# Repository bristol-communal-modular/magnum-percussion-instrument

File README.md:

# The Magnum Percussion Instrument

A drum synthesiser created by members of the Bristol Communal Modular group

## Description

Mostly combining bits from other open source schematics.

Specifically :-

* The Clacktronics Star Synare 3
* The Befaco Kickall

Many thanks to the people that designed those and made them open.

## Building

In the *build* folder there's an html BOM file, along with a CSV file that has part numbers for most components. Read the build.md file in there for more information. If you're reading this on GitHub and are unsure how to easily get these files, then [use this link](https://github.com/bristol-communal-modular/magnum-percussion-instrument/archive/refs/heads/main.zip)

## Spec

*Finish this*

### Power

30mA on +12v
30mA on -12v

Doesn't use 5v

## Contact

Come down the Bristol Hackspace on a Tuesday night to say hello.

## License

The Magnum Percussion Instrument is shared under an [Attribution-NonCommercial-ShareAlike 4.0 International License](https://creativecommons.org/licenses/by-nc-sa/4.0/)

This means that you can share the info here around, and transform or build upon the circuits and designs in here, as long as you share anything you do under the same license and give BCM a shout-out.

We don't license this for commercial purposes, but if you'd like to run a workshop with the Magnum or some variation of it, just get in contact and we can sort something out.
If you want to build a couple to sell to your mates then we're pretty fine with that as well.

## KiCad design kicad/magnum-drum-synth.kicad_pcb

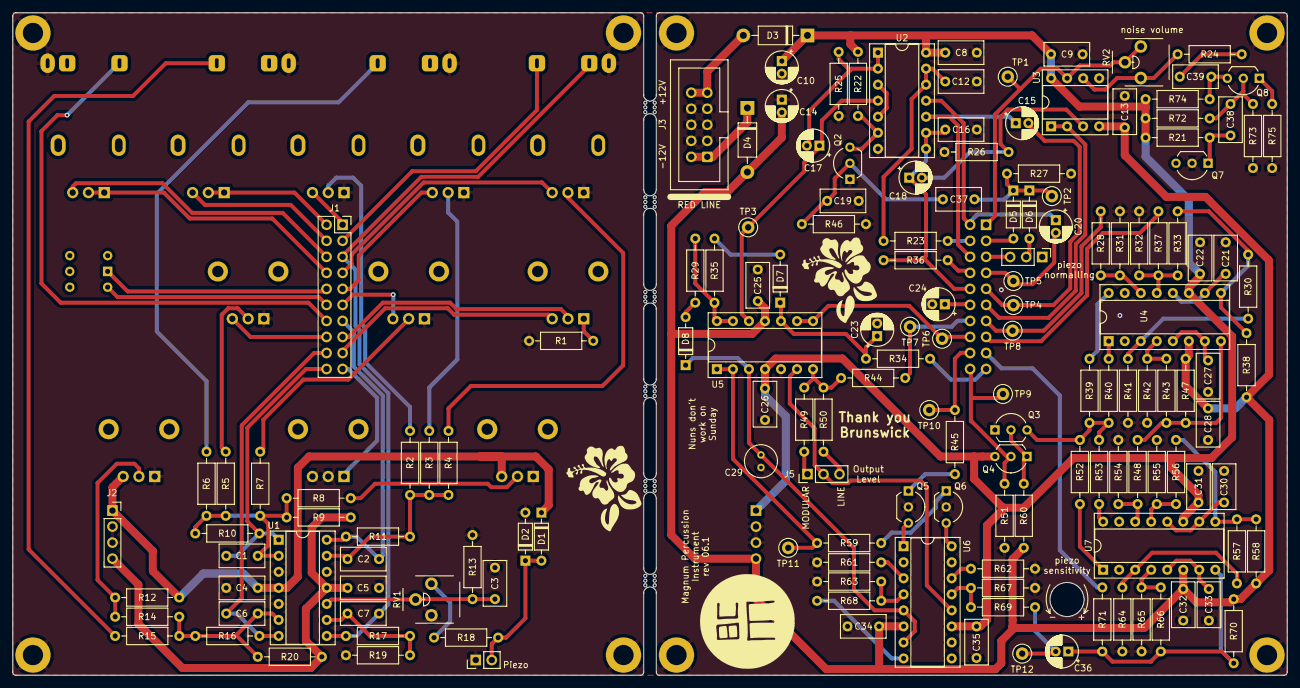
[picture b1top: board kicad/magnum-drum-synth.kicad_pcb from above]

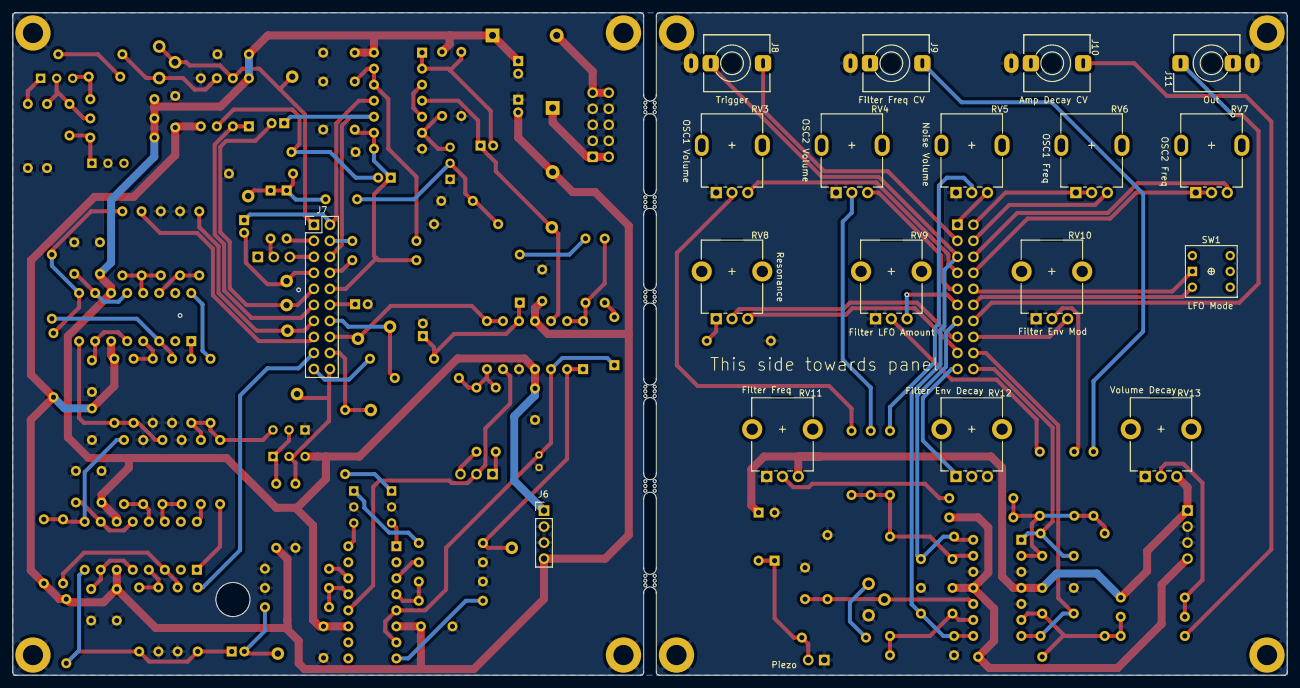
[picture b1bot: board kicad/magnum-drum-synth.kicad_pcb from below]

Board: 2 copper layers, 202.0 x 105.0 mm, 188 parts (18 on the bottom side), 119 nets.

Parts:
C1, C19: 10nF; C_Rect_L7.0mm_W3.5mm_P5.00mm
C2, C6, C7: 22pF; C_Rect_L7.0mm_W3.5mm_P5.00mm
C3: 220nF; C_Rect_L7.0mm_W3.5mm_P5.00mm
C4, C5, C8, C9, C13, C22, C25, C26, C28, C31, C32, C34, C35, C37, C38, C39: 100nF; C_Rect_L7.0mm_W3.5mm_P5.00mm
C10, C14, C23, C36: 10uF; CP_Radial_D5.0mm_P2.00mm
C12, C16: 47nF; C_Rect_L7.0mm_W3.5mm_P5.00mm
C15, C17, C18, C20, C24: 1uF; CP_Radial_D5.0mm_P2.00mm
C21, C27, C30, C33: 100pF; C_Rect_L7.0mm_W3.5mm_P5.00mm
C29: 1uF; C_Radial_D5.0mm_H5.0mm_P2.00mm
D1, D2, D5, D6, D7, D8: 1N4148; D_DO-35_SOD27_P7.62mm_Horizontal
D3, D4: 1N5818; D_DO-41_SOD81_P10.16mm_Horizontal
H1, H2, H9, H10, H13, H14, H15, H16: MountingHole_Pad; MountingHole_3.2mm_M3_DIN965_Pad
H3, H4, H5, H6, H7, H8: MouseBite; mouse-bite-2mm-slot
J1: Conn_02x10_Odd_Even; PinSocket_2x10_P2.54mm_Vertical
J2: Conn_01x04_Socket; PinSocket_1x04_P2.54mm_Vertical
J3: locked; Eurorack_PowerHeader_2x05_P2.54mm_Shrouded
J4, J5: Conn_01x03_Header; PinHeader_1x03_P2.54mm_Vertical
J6: Conn_01x04_Header; PinHeader_1x04_P2.54mm_Vertical
J7: Conn_02x10_Odd_Even; PinHeader_2x10_P2.54mm_Vertical
J8, J9, J10, J11: Eurorack Mono Jack; Jack_3.5mm_QingPu_WQP-PJ398SM_Vertical
MK1: Piezo; PinHeader_1x02_P2.54mm_Vertical
Q2, Q4, Q7, Q8: 2N3904; TO-92_Inline_Wide
Q3, Q5, Q6: 2N3906; TO-92_Inline_Wide
R1, R5: 47k; R_Axial_DIN0207_L6.3mm_D2.5mm_P10.16mm_Horizontal
R2, R3, R4, R6, R7, R8, R11, R15, R20, R21, R27, R28, R30, R33, R43, R48, R56, R57, R60, R66, R69, R73: 100k; R_Axial_DIN0207_L6.3mm_D2.5mm_P10.16mm_Horizontal
R9, R26: 220k; R_Axial_DIN0207_L6.3mm_D2.5mm_P10.16mm_Horizontal
R10: 2k; R_Axial_DIN0207_L6.3mm_D2.5mm_P10.16mm_Horizontal
R12, R23, R36, R39, R40, R52, R53: 22k; R_Axial_DIN0207_L6.3mm_D2.5mm_P10.16mm_Horizontal
R13: 1m; R_Axial_DIN0207_L6.3mm_D2.5mm_P10.16mm_Horizontal
R14: 120k; R_Axial_DIN0207_L6.3mm_D2.5mm_P10.16mm_Horizontal
R16: 27k; R_Axial_DIN0207_L6.3mm_D2.5mm_P10.16mm_Horizontal
R17, R68: 33k; R_Axial_DIN0207_L6.3mm_D2.5mm_P10.16mm_Horizontal
R18, R34, R51: 1k; R_Axial_DIN0207_L6.3mm_D2.5mm_P10.16mm_Horizontal
R19, R22, R24, R25, R38, R46, R47, R58, R70, R71, R74: 10k; R_Axial_DIN0207_L6.3mm_D2.5mm_P10.16mm_Horizontal
R29: 100r; R_Axial_DIN0207_L6.3mm_D2.5mm_P10.16mm_Horizontal
R31, R32, R41, R42, R54, R55, R62, R64, R65, R67: 220r; R_Axial_DIN0207_L6.3mm_D2.5mm_P10.16mm_Horizontal
R35: 47r; R_Axial_DIN0207_L6.3mm_D2.5mm_P10.16mm_Horizontal
R37: 6k8; R_Axial_DIN0207_L6.3mm_D2.5mm_P10.16mm_Horizontal
R44, R61, R63: 470r; R_Axial_DIN0207_L6.3mm_D2.5mm_P10.16mm_Horizontal
R45: 4k7; R_Axial_DIN0207_L6.3mm_D2.5mm_P10.16mm_Horizontal
R49: 56k; R_Axial_DIN0207_L6.3mm_D2.5mm_P10.16mm_Horizontal
R50: 12k; R_Axial_DIN0207_L6.3mm_D2.5mm_P10.16mm_Horizontal
R59: 18k; R_Axial_DIN0207_L6.3mm_D2.5mm_P10.16mm_Horizontal
R72: 560k; R_Axial_DIN0207_L6.3mm_D2.5mm_P10.16mm_Horizontal
R75: 22r; R_Axial_DIN0207_L6.3mm_D2.5mm_P10.16mm_Horizontal
RV1: 100k; Potentiometer_THT_Bourns_3306P_Vertical
RV2: 1m; Potentiometer_THT_Bourns_3306P_Vertical
RV3, RV4, RV5: 100kA; Potentiometer_Song_Huei_R0904N_Single_Vertical
RV6, RV7: 1mA; Potentiometer_Song_Huei_R0904N_Single_Vertical
RV8: 50kB; Potentiometer_Alpha_RD901F-40-00D_Single_Vertical_CircularH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
RV9, RV10, RV11, RV12, RV13: 100kB; Potentiometer_Alpha_RD901F-40-00D_Single_Vertical_CircularH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
Ref**1: Val**; BCM_Logo_small_15mmx15mm
SW1: DPDT; SW_PUSH_2P2T_8mm_Apem_MHPS2285
TP1: Noise TestPoint; TestPoint_Loop_D2.50mm_Drill1.0mm_LowProfile
TP2: Trigger TestPoint; TestPoint_Loop_D2.50mm_Drill1.0mm_LowProfile
TP3, TP10: Schmitt Trigger TestPoint; TestPoint_Loop_D2.50mm_Drill1.0mm_LowProfile
TP4: OSC2 TestPoint; TestPoint_Loop_D2.50mm_Drill1.0mm_LowProfile
TP5: OSC1 TestPoint; TestPoint_Loop_D2.50mm_Drill1.0mm_LowProfile
TP6: Filter Envelope TestPoint; TestPoint_Loop_D2.50mm_Drill1.0mm_LowProfile
TP7: Final Output TestPoint; TestPoint_Loop_D2.50mm_Drill1.0mm_LowProfile
TP8: Mixer TestPoint; TestPoint_Loop_D2.50mm_Drill1.0mm_LowProfile
TP9: Filter CV Mixer TestPoint; TestPoint_Loop_D2.50mm_Drill1.0mm_LowProfile
TP11: VCA Envelope TestPoint; TestPoint_Loop_D2.50mm_Drill1.0mm_LowProfile
TP12: Filter Output TestPoint; TestPoint_Loop_D2.50mm_Drill1.0mm_LowProfile
U1, U5: TL074; DIP-14_W7.62mm_Socket
U2: CD4093; DIP-14_W7.62mm_Socket
U3: TL072; DIP-8_W7.62mm_Socket
U4, U6, U7: LM13700; DIP-16_W7.62mm_Socket

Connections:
+12V: C4.1, C8.1, C9.1, C10.1, C22.1, C26.1, C31.1, C35.1, D1.1 (K), D3.1 (K), J2.1, J6.1, Q4.3 (C), R12.2, R21.1, R22.1, R72.2, R74.2, RV11.3, RV13.3, U1.4 (V+), U2.14 (VCC), U3.8 (V+), U4.11 (V+), U5.4 (V+), U6.11 (V+), U7.11 (V+)
-12V: C5.2, C13.2, C14.2, C25.2, C28.2, C32.2, C34.2, D4.2 (A), J2.4, J6.4, R9.1, R20.1, R38.2, R47.2, R58.2, R60.1, R70.2, U1.11 (V-), U3.4 (V-), U4.6 (V-), U5.11 (V-), U6.6 (V-), U7.6 (V-)
/AMP_DECAY_CV_MIX_CTRL: C6.2, J1.18, R16.2, U1.7
/AMP_DECAY_CV_MIX_MAIN: J7.18, R45.1, TP10.1
/FILTER_ENV_DECAY_CTRL: J1.19, RV12.1
/FILTER_ENV_DECAY_MAIN: J7.19, R34.2
/FILTER_ENV_MOD_CTRL: J1.16, RV10.3
/FILTER_ENV_MOD_MAIN: J7.16, TP6.1, U5.8, U5.9 (-)
/FILTER_FREQ_CV_CTRL: C1.2, J1.20, R10.2, U1.1
/FILTER_FREQ_CV_MAIN: J7.20, Q4.2 (B), R51.1, TP9.1
/FINAL_OUTPUT_CTRL: J1.14, J11.2 (Tip)
/FINAL_OUTPUT_MAIN: J7.14, R44.2, TP7.1
/Filter/I_Freq: Q3.3 (C), R39.2, R40.2, R52.2, R53.2
/Filter/Output: C36.1, R66.2, R70.1, R71.1, U7.8
/MIX_RETURN_CTRL: C2.2, J1.13, R11.2, U1.14
/MIX_RETURN_MAIN: J7.13, R28.1, TP8.1
/NOISE_SIGNAL_CTRL: J1.1, RV5.3
/NOISE_SIGNAL_MAIN: J7.1, RV2.2, RV2.3, TP1.1, U3.7
/OSC1_FREQ_L_CTRL: J1.4, RV6.3
/OSC1_FREQ_L_MAIN: J7.4, R23.2
/OSC1_FREQ_R_CTRL: J1.2, RV6.1, RV6.2
/OSC1_FREQ_R_MAIN: C20.1, J7.2, U2.11
/OSC1_SIGNAL_CTRL: J1.7, RV3.3
/OSC1_SIGNAL_MAIN: C20.2, J7.7, TP5.1
/OSC2_FILTER_MOD_CTRL: J1.11, RV9.3
/OSC2_FILTER_MOD_MAIN: J7.11, U3.1, U3.2 (-)
/OSC2_FREQ_L_CTRL: J1.8, RV7.1, RV7.2
/OSC2_FREQ_L_MAIN: J7.8, R36.2
/OSC2_FREQ_R_CTRL: J1.6, RV7.3
/OSC2_FREQ_R_MAIN: C15.1, J7.6, U2.10
/OSC2_LFO_CAP_CTRL: J1.12, SW1.2 (B)
/OSC2_LFO_CAP_MAIN: C24.1, J7.12
/OSC2_LFO_CTRL: J1.10, SW1.1 (A)
/OSC2_LFO_MAIN: C16.1, C18.1, J7.10, R36.1, U2.8, U2.9
/OSC2_SIGNAL_CTRL: J1.9, RV4.3
/OSC2_SIGNAL_MAIN: C15.2, J7.9, TP4.1
/OutputVCA/I_Gain: Q6.3 (C), U6.16
/OutputVCA/Input: C36.2, R69.1, TP12.1
/OutputVCA/Output: R44.1, R49.2, R50.2, U5.7
/PIEZO_CTRL: C7.2, J1.5, J8.3 (Tip_normalize), R17.1, U1.8
/PIEZO_MAIN: J4.3, J7.5
/RES_AMOUNT_CTRL: J1.15, RV8.2
/RES_AMOUNT_MAIN: J7.15, R37.1
/RES_TOP_CTRL: J1.17, RV8.3
/RES_TOP_MAIN: J7.17, R71.2
/TRIG_IN_CTRL: J1.3, J8.2 (Tip)
/TRIG_IN_MAIN: D5.2 (A), J7.3
/Trigger: R29.1, R35.1, U5.13 (-), U5.14
GND: C3.1, C4.2, C5.1, C8.2, C9.2, C10.2, C12.1, C13.1, C14.1, C16.2, C19.1, C21.1, C22.2, C23.2, C24.2, C25.1, C26.2, C27.1, C28.1, C29.2, C30.1, C31.2, C32.1, C33.1, C34.1, C35.2, D2.2 (A), H1.1, H2.1, H9.1, H10.1, H13.1, H14.1, H15.1, H16.1, J2.2, J2.3, J3.3 (GND), J3.4 (GND), J3.5 (GND), J3.6 (GND), J3.7 (GND), J3.8 (GND), J6.2, J6.3, J8.1 (Sleeve), J9.1 (Sleeve), J10.1 (Sleeve), J11.1 (Sleeve), MK1.1 (-), Q2.1 (E), Q3.1 (E), Q5.2 (B), Q6.2 (B), Q7.2 (B), R1.2, R13.2, R19.1, R25.2, R26.1, R27.1, R31.2, R32.2, R41.2, R42.2, R46.2, R51.2, R54.2, R55.2, R61.1, R62.2, R63.1, R64.2, R65.2, R67.2, R73.1, R75.1, RV1.1, RV3.1, RV4.1, RV5.1, RV9.1, RV10.1, RV11.1, RV12.2, RV12.3, RV13.1, U1.3 (+), U1.5 (+), U1.12 (+), U2.7 (GND), U3.5 (+), U5.5 (+)
unnamed: C12.2, R23.1, U2.12, U2.13
unnamed: C17.2, R25.1, U2.1, U2.2
unnamed: C21.2, U4.10, U4.12
unnamed: C27.2, U4.5, U4.7
unnamed: C30.2, U7.10, U7.12
unnamed: C33.2, U7.5, U7.7
unnamed: C39.2, R24.1
unnamed: D1.2 (A), D2.1 (K), MK1.2 (+), R18.1
unnamed: D3.2 (A), J3.9 (+12V), J3.10 (+12V)
unnamed: D4.1 (K), J3.1 (-12V), J3.2 (-12V)
unnamed: C37.2, D5.1 (K), D6.1 (K), R27.2, TP2.1
unnamed: D6.2 (A), J4.2
unnamed: D7.2 (A), R35.2
unnamed: C23.1, D7.1 (K), R34.1, U5.10 (+)
unnamed: D8.2 (A), R29.2
unnamed: C29.1, D8.1 (K), U5.3 (+), U6.5, U6.7
unnamed: J5.1, R49.1
unnamed: J5.2, U5.6 (-), U6.12
unnamed: J5.3, R50.1
unnamed: J9.2 (Tip), R6.1
unnamed: J10.2 (Tip), R15.1
unnamed: C19.2, C37.1, Q2.2 (B), R46.1
unnamed: Q2.3 (C), R22.2, U2.6
unnamed: Q3.2 (B), Q4.1 (E), R60.2
unnamed: Q5.3 (C), U6.1
unnamed: Q5.1 (E), R45.2
unnamed: Q6.1 (E), R59.2
unnamed: C38.1, Q7.1 (E), R21.2
unnamed: C38.2, Q8.2 (B), R72.1, R73.2
unnamed: C39.1, Q8.3 (C), R74.1
unnamed: Q8.1 (E), R75.2
unnamed: R1.1, RV8.1
unnamed: R2.1, RV5.2
unnamed: R3.1, RV4.2
unnamed: R4.1, RV3.2
unnamed: R5.1, RV10.2
unnamed: R7.1, RV9.2
unnamed: R8.1, RV11.2
unnamed: R12.1, R14.2, RV13.2
unnamed: R18.2, RV1.3
unnamed: R30.1, R33.2, R38.1, U4.9
unnamed: R39.1, U4.16
unnamed: R40.1, U4.1
unnamed: R43.2, R47.1, R48.1, U4.8
unnamed: R52.1, U7.1
unnamed: R53.1, U7.16
unnamed: R56.2, R57.1, R58.1, U7.9
unnamed: R68.2, U6.8
unnamed: C1.1, R5.2, R6.2, R7.2, R8.2, R9.2, R10.1, U1.2 (-)
unnamed: C6.1, R14.1, R15.2, R16.1, R20.2, U1.6 (-)
unnamed: C3.2, R13.1, RV1.2, U1.10 (+)
unnamed: C7.1, R17.2, R19.2, U1.9 (-)
unnamed: C2.1, R2.2, R3.2, R4.2, R11.1, U1.13 (-)
unnamed: U2.3, U2.5
unnamed: C18.2, R26.2, U3.3 (+)
unnamed: R24.2, RV2.1, U3.6 (-)
unnamed: R28.2, R31.1, U4.14 (+)
unnamed: R32.1, R33.1, R37.2, U4.13 (-)
unnamed: R30.2, R41.1, U4.3 (+)
unnamed: R42.1, R43.1, U4.4 (-)
unnamed: R59.1, TP11.1, U5.1, U5.2 (-)
unnamed: C17.1, TP3.1, U2.4, U5.12 (+)
unnamed: R62.1, U6.14 (+)
unnamed: R67.1, R69.2, U6.13 (-)
unnamed: R61.2, U6.3 (+)
unnamed: R63.2, R68.1, U6.4 (-)
unnamed: R48.2, R54.1, U7.14 (+)
unnamed: R55.1, R56.1, U7.13 (-)
unnamed: R57.2, R64.1, U7.3 (+)
unnamed: R65.1, R66.1, U7.4 (-)

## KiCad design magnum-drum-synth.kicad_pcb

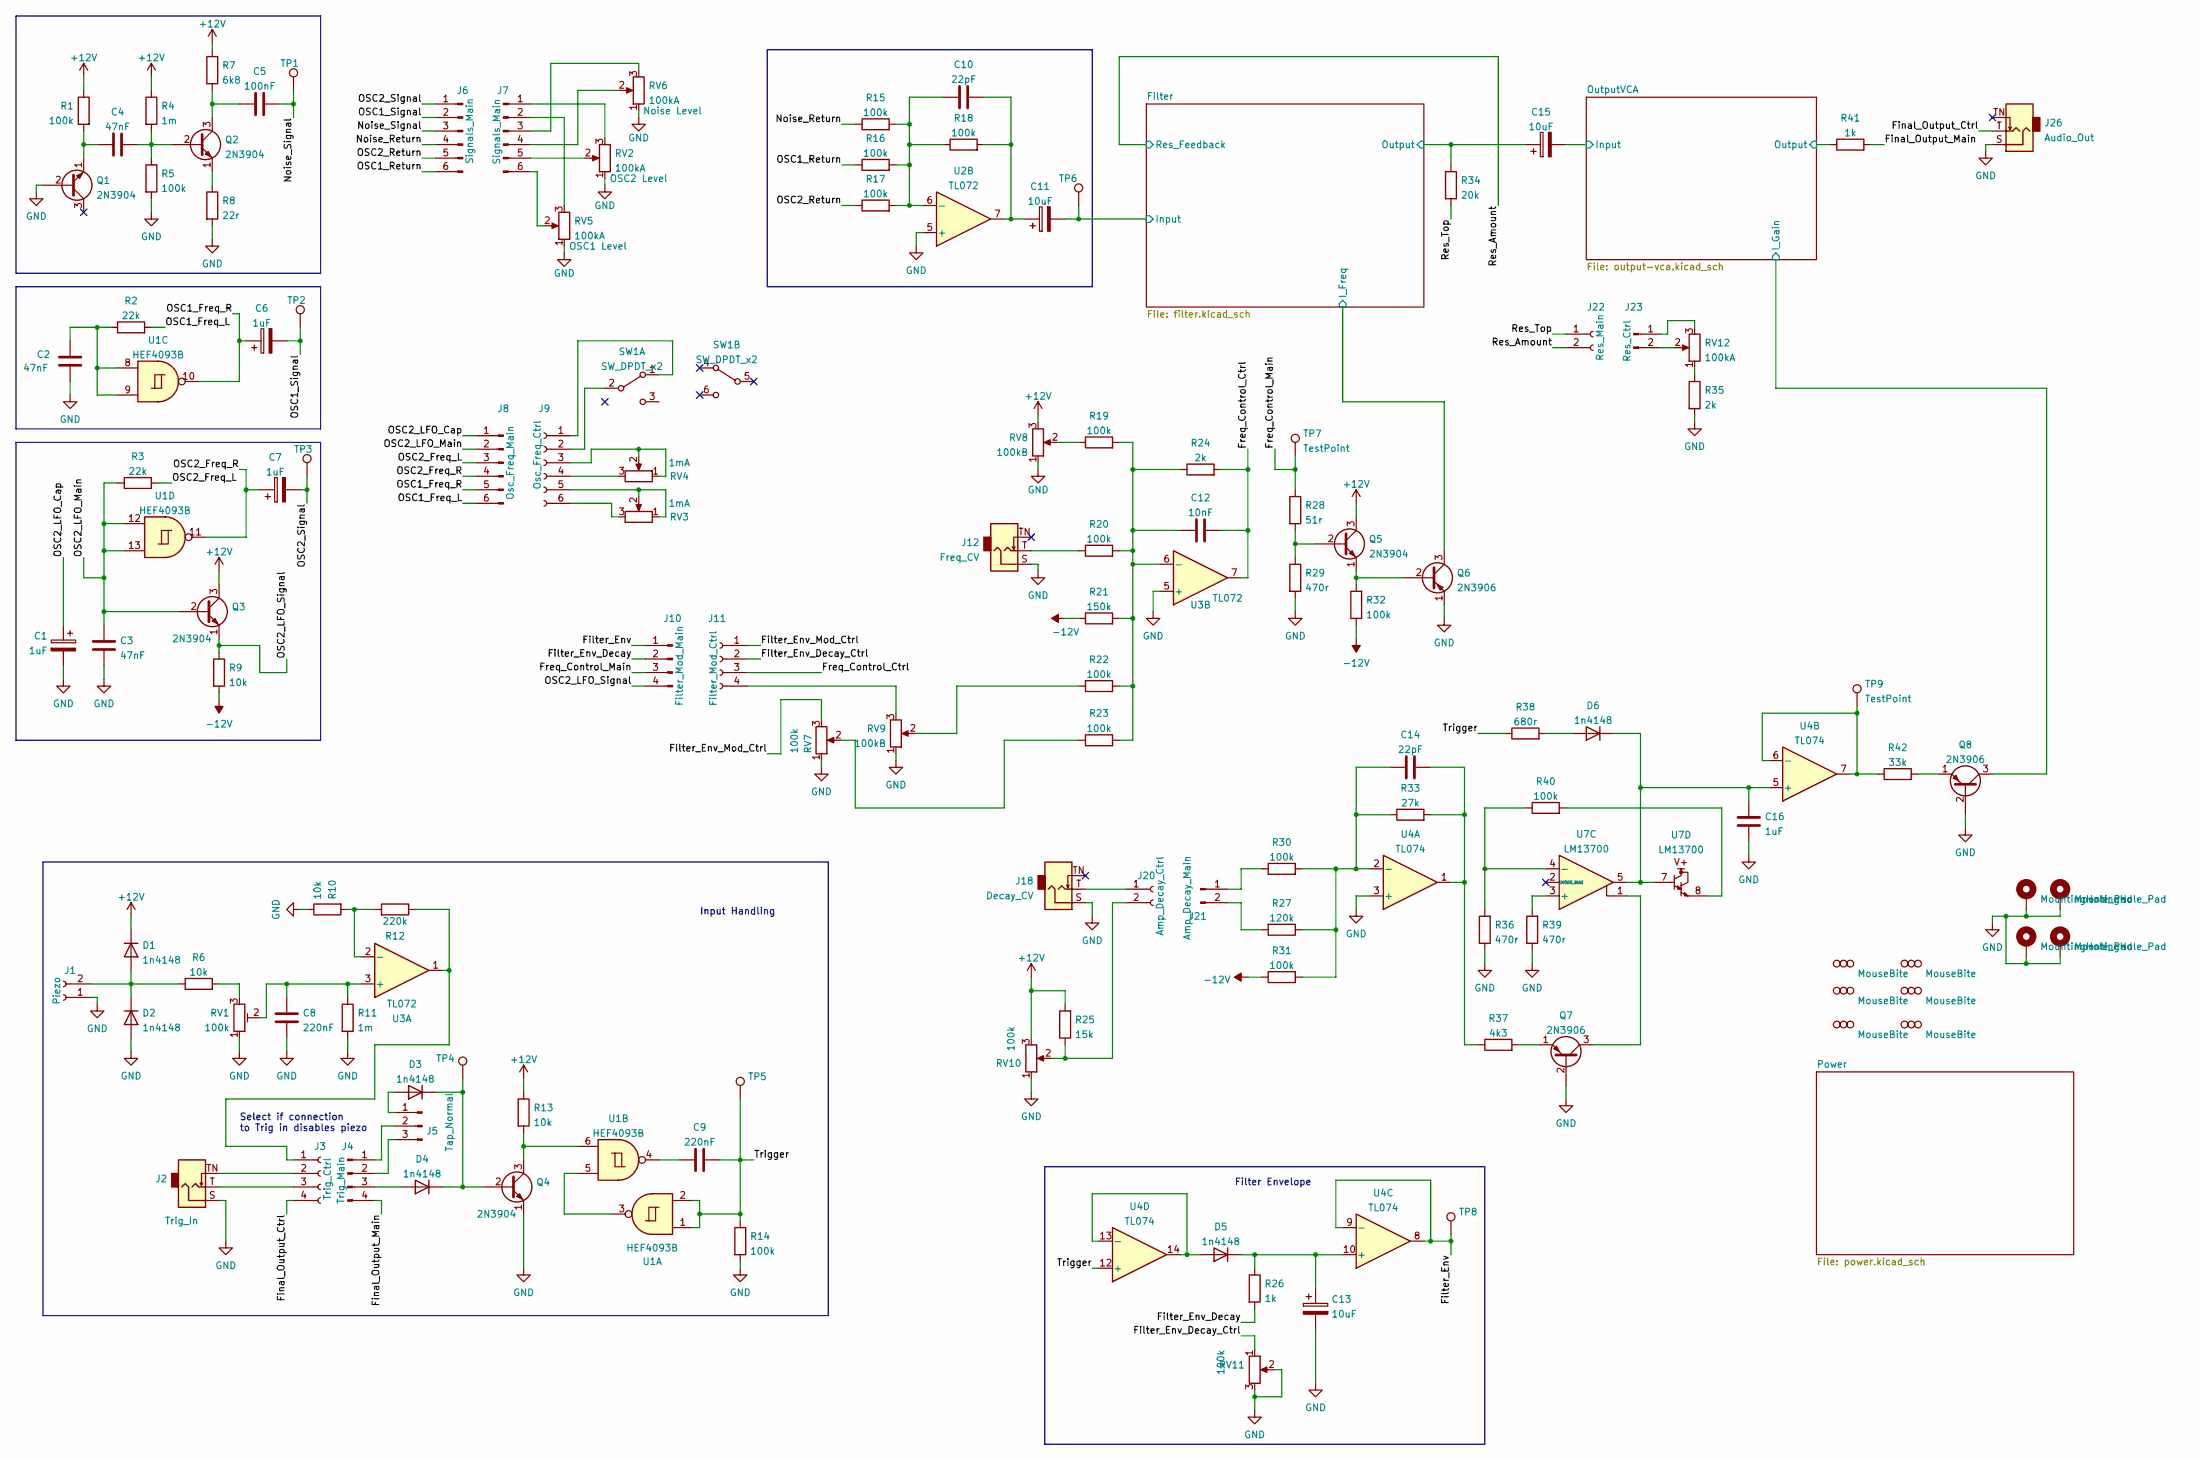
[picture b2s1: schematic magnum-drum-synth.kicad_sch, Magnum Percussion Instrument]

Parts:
C1, C6, C7: 1uF; CP_Radial_D5.0mm_P2.50mm
C2, C3, C4: 47nF; C_Rect_L7.0mm_W3.5mm_P5.00mm
C5: 100nF; C_Rect_L7.0mm_W3.5mm_P5.00mm
C8, C9: 220nF; C_Rect_L7.0mm_W3.5mm_P5.00mm
C10, C14: 22pF; C_Rect_L7.0mm_W3.5mm_P5.00mm
C11, C13, C15: 10uF; CP_Radial_D5.0mm_P2.50mm
C12: 10nF; C_Rect_L7.0mm_W3.5mm_P5.00mm
C16: 1uF; C_Radial_D6.3mm_H7.0mm_P2.50mm
D1, D2, D3, D4, D5, D6: 1n4148; Diode_THT_P7.62mm_Horizontal
H1, H2, H3, H4, H5, H6: MouseBite; mouse-bite-2mm-slot
H7, H8, H9, H10: MountingHole_Pad; MountingHole_3.2mm_M3_ISO7380_Pad
J1: Piezo; PinHeader_1x02_P2.54mm_Vertical
J2: Trig_In; Jack_3.5mm_QingPu_WQP-PJ398SM_Vertical
J3: Trig_Ctrl; PinSocket_1x04_P2.54mm_Vertical
J4: Trig_Main; PinHeader_1x04_P2.54mm_Vertical
J5: Tap_Normal; PinHeader_1x03_P2.54mm_Vertical
J6, J7: Signals_Main; PinSocket_1x06_P2.54mm_Vertical
J8: Osc_Freq_Main; PinHeader_1x06_P2.54mm_Vertical
J9: Osc_Freq_Ctrl; PinSocket_1x06_P2.54mm_Vertical
J10: Filter_Mod_Main; PinSocket_1x04_P2.54mm_Vertical
J11: Filter_Mod_Ctrl; PinSocket_1x04_P2.54mm_Vertical
J12: Freq_CV; Jack_3.5mm_QingPu_WQP-PJ398SM_Vertical
J18: Decay_CV; Jack_3.5mm_QingPu_WQP-PJ398SM_Vertical
J20: Amp_Decay_Ctrl; PinSocket_1x02_P2.54mm_Vertical
J21: Amp_Decay_Main; PinHeader_1x02_P2.54mm_Vertical
J22: Res_Main; PinHeader_1x02_P2.54mm_Vertical
J23: Res_Ctrl; PinSocket_1x02_P2.54mm_Vertical
J26: Audio_Out; Jack_3.5mm_QingPu_WQP-PJ398SM_Vertical
Q1, Q2, Q3, Q4, Q5: 2N3904; TO-92_Inline_Wide
Q6, Q7, Q8: 2N3906; TO-92_Inline_Wide
R1, R5, R14, R15, R16, R17, R18, R19, R20, R22, R23, R30, R31, R32, R40: 100k; Resistor_THT_L6.3mm_D2.5mm_P10.16mm_Horizontal
R2, R3: 22k; Resistor_THT_L6.3mm_D2.5mm_P10.16mm_Horizontal
R4, R11: 1m; Resistor_THT_L6.3mm_D2.5mm_P10.16mm_Horizontal
R6, R9, R10, R13: 10k; Resistor_THT_L6.3mm_D2.5mm_P10.16mm_Horizontal
R7: 6k8; Resistor_THT_L6.3mm_D2.5mm_P10.16mm_Horizontal
R8: 22r; Resistor_THT_L6.3mm_D2.5mm_P10.16mm_Horizontal
R12: 220k; Resistor_THT_L6.3mm_D2.5mm_P10.16mm_Horizontal
R21: 150k; Resistor_THT_L6.3mm_D2.5mm_P10.16mm_Horizontal
R24, R35: 2k; Resistor_THT_L6.3mm_D2.5mm_P10.16mm_Horizontal
R25: 15k; Resistor_THT_L6.3mm_D2.5mm_P10.16mm_Horizontal
R26, R41: 1k; Resistor_THT_L6.3mm_D2.5mm_P10.16mm_Horizontal
R27: 120k; Resistor_THT_L6.3mm_D2.5mm_P10.16mm_Horizontal
R28: 51r; Resistor_THT_L6.3mm_D2.5mm_P10.16mm_Horizontal
R29, R36, R39: 470r; Resistor_THT_L6.3mm_D2.5mm_P10.16mm_Horizontal
R33: 27k; Resistor_THT_L6.3mm_D2.5mm_P10.16mm_Horizontal
R34: 20k; Resistor_THT_L6.3mm_D2.5mm_P10.16mm_Horizontal
R37: 4k3; Resistor_THT_L6.3mm_D2.5mm_P10.16mm_Horizontal
R38: 680r; Resistor_THT_L6.3mm_D2.5mm_P10.16mm_Horizontal
R42: 33k; Resistor_THT_L6.3mm_D2.5mm_P10.16mm_Horizontal
RV1: 100k; Potentiometer_THT_Bourns_3306P_Vertical
RV2, RV5, RV6: 100kA; Potentiometer_Alpha_RD901F-40-00D_Single_Vertical
RV3, RV4: 1mA; Potentiometer_Alpha_RD901F-40-00D_Single_Vertical
RV7, RV10, RV11: 100k; Potentiometer_Alpha_RD901F-40-00D_Single_Vertical_CircularH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
RV8, RV9: 100kB; Potentiometer_Alpha_RD901F-40-00D_Single_Vertical_CircularH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
RV12: 100kA; Potentiometer_Alpha_RD901F-40-00D_Single_Vertical_CircularH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
SW1: SW_DPDT_x2; SW_PUSH_2P2T_8mm_Apem_MHPS2285
TP1: Noise TestPoint; TestPoint_Loop_D2.50mm_Drill1.0mm_LowProfile
TP2: OSC1 TestPoint; TestPoint_Loop_D2.50mm_Drill1.0mm_LowProfile
TP3: OSC2 TestPoint; TestPoint_Loop_D2.50mm_Drill1.0mm_LowProfile
TP4: Trigger TestPoint; TestPoint_Loop_D2.50mm_Drill1.0mm_LowProfile
TP5: Schmitt Trigger TestPoint; TestPoint_Loop_D2.50mm_Drill1.0mm_LowProfile
TP6: Mixer TestPoint; TestPoint_Loop_D2.50mm_Drill1.0mm_LowProfile
TP7, TP9: TestPoint; TestPoint_Loop_D2.50mm_Drill1.0mm_LowProfile
TP8: Filter Env TestPoint; TestPoint_Loop_D2.50mm_Drill1.0mm_LowProfile
U1: HEF4093B; DIP-14_W7.62mm_LongPads
U2, U3: TL072; DIP-8_W7.62mm_LongPads
U4: TL074; DIP-14_W7.62mm_LongPads
U7: LM13700; DIP-16_W7.62mm_LongPads

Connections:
+12V: D1.1 (K), Q3.3 (C), Q5.3 (C), R1.1, R4.1, R7.1, R13.1, R25.2, RV8.3, RV10.3; also elsewhere on the board
-12V: R9.2, R21.1, R31.1, R32.1; also elsewhere on the board
/Filter/I_Freq: Q6.3 (C); also elsewhere on the board
/Filter/Input: C11.2, TP6.1; also elsewhere on the board
/Filter/Output: C15.1, R34.1; also elsewhere on the board
/Filter_Env: J10.1, TP8.1, U4.8, U4.9 (-)
/Filter_Env_Decay: J10.2, R26.2
/Filter_Env_Decay_Ctrl: J11.2, RV11.1
/Filter_Env_Mod_Ctrl: J11.1, RV7.3
/Final_Output_Ctrl: J3.4, J26.T
/Final_Output_Main: J4.4, R41.2
/Freq_Control_Ctrl: C12.2, J11.3, R24.2, U3.7
/Freq_Control_Main: J10.3, R28.1, TP7.1
/Noise_Return: J6.4, R15.1
/Noise_Signal: C5.2, J6.3, TP1.1
/OSC1_Freq_L: J8.6, R2.2
/OSC1_Freq_R: C6.1, J8.5, U1.10
/OSC1_Return: J6.6, R16.1
/OSC1_Signal: C6.2, J6.2, TP2.1
/OSC2_Freq_L: J8.3, R3.2
/OSC2_Freq_R: C7.1, J8.4, U1.11
/OSC2_LFO_Cap: C1.1, J8.1
/OSC2_LFO_Main: C3.1, J8.2, Q3.2 (B), R3.1, U1.12, U1.13
/OSC2_LFO_Signal: J10.4, Q3.1 (E), R9.1
/OSC2_Return: J6.5, R17.1
/OSC2_Signal: C7.2, J6.1, TP3.1
/OutputVCA/I_Gain: Q8.3 (C); also elsewhere on the board
/OutputVCA/Input: C15.2; also elsewhere on the board
/OutputVCA/Output: R41.1; also elsewhere on the board
/Res_Amount: J22.2; also elsewhere on the board
/Res_Top: J22.1, R34.2
/Trigger: C9.2, R14.1, R38.1, TP5.1, U1.1, U1.2, U4.12 (+)
GND: C1.2, C2.1, C3.2, C8.1, C13.2, C16.2, D2.2 (A), H7.1, H8.1, H9.1, H10.1, J1.1, J2.S, J12.S, J18.S, J26.S, Q1.2 (B), Q4.1 (E), Q6.1 (E), Q7.2 (B), Q8.2 (B), R5.2, R8.2, R10.1, R11.2, R14.2, R29.2, R35.2, R36.1, R39.1, RV1.1, RV2.1, RV5.1, RV6.1, RV7.1, RV8.1, RV9.1, RV10.1, RV11.2, RV11.3, U2.5 (+), U3.5 (+), U4.3 (+); also elsewhere on the board
unnamed: C2.2, R2.1, U1.8, U1.9
unnamed: C4.1, Q1.1 (E), R1.2
unnamed: C4.2, Q2.2 (B), R4.2, R5.1
unnamed: C5.1, Q2.3 (C), R7.2
unnamed: C8.2, R11.1, RV1.2, U3.3 (+)
unnamed: C9.1, U1.4
unnamed: C10.1, R15.2, R16.2, R17.2, R18.1, U2.6 (-)
unnamed: C10.2, C11.1, R18.2, U2.7
unnamed: C12.1, R19.2, R20.2, R21.2, R22.2, R23.2, R24.1, U3.6 (-)
unnamed: C13.1, D5.1 (K), R26.1, U4.10 (+)
unnamed: C14.1, R27.1, R30.2, R31.2, R33.1, U4.2 (-)
unnamed: C14.2, R33.2, R37.1, U4.1
unnamed: C16.1, D6.1 (K), U4.5 (+), U7.5, U7.7
unnamed: D1.2 (A), D2.1 (K), J1.2, R6.1
unnamed: D3.1 (K), D4.1 (K), Q4.2 (B), TP4.1
unnamed: D3.2 (A), J5.1
unnamed: D4.2 (A), J4.3
unnamed: D5.2 (A), U4.13 (-), U4.14
unnamed: D6.2 (A), R38.2
unnamed: J2.T, J3.3
unnamed: J2.TN, J3.2
unnamed: J3.1, R12.1, U3.1
unnamed: J4.1, J5.2
unnamed: J4.2, J5.3
unnamed: J7.1, RV2.3
unnamed: J7.2, RV5.3
unnamed: J7.3, RV6.3
unnamed: J7.4, RV6.2
unnamed: J7.5, RV2.2
unnamed: J7.6, RV5.2
unnamed: J9.1, SW1.1 (A)
unnamed: J9.2, SW1.2 (B)
unnamed: J9.3, RV4.1, RV4.2
unnamed: J9.4, RV4.3
unnamed: J9.5, RV3.1, RV3.2
unnamed: J9.6, RV3.3
unnamed: J11.4, RV9.3
unnamed: J12.T, R20.1
unnamed: J18.T, J20.1
unnamed: J20.2, R25.1, RV10.2
unnamed: J21.1, R30.1
unnamed: J21.2, R27.2
unnamed: J23.1, RV12.3
unnamed: J23.2, RV12.2
unnamed: Q2.1 (E), R8.1
unnamed: Q4.3 (C), R13.2, U1.6
unnamed: Q5.1 (E), Q6.2 (B), R32.2
unnamed: Q5.2 (B), R28.2, R29.1
unnamed: Q7.1 (E), R37.2
unnamed: Q7.3 (C), U7.1
unnamed: Q8.1 (E), R42.2
unnamed: R6.2, RV1.3
unnamed: R10.2, R12.2, U3.2 (-)
unnamed: R19.1, RV8.2
unnamed: R22.1, RV9.2
unnamed: R23.1, RV7.2
unnamed: R35.1, RV12.1
unnamed: R36.2, R40.1, U7.4 (-)
unnamed: R39.2, U7.3 (+)
unnamed: R40.2, U7.8
unnamed: R42.1, TP9.1, U4.6 (-), U4.7
unnamed: U1.3, U1.5

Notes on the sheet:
Input Handling
Filter Envelope
Select if connection to Trig in disables piezo

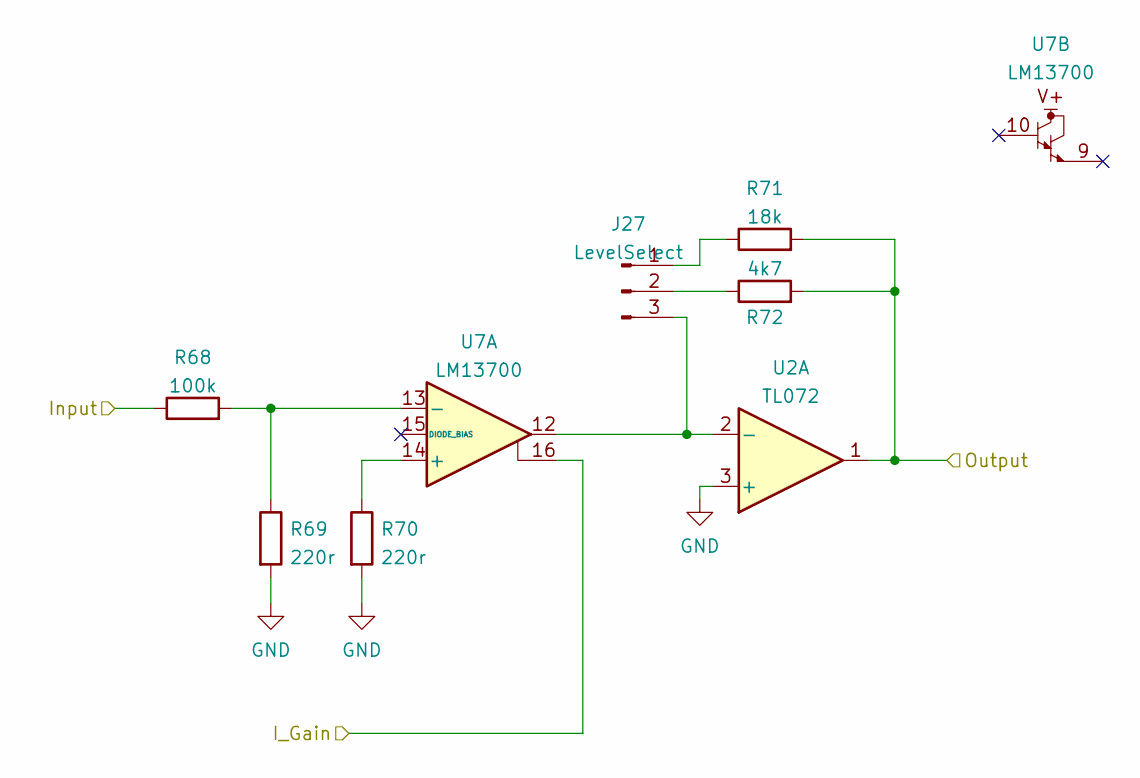
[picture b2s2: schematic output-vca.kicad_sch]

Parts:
J27: LevelSelect; PinHeader_1x03_P2.54mm_Vertical
R68: 100k; Resistor_THT_L6.3mm_D2.5mm_P10.16mm_Horizontal
R69, R70: 220r; Resistor_THT_L6.3mm_D2.5mm_P10.16mm_Horizontal
R71: 18k; Resistor_THT_L6.3mm_D2.5mm_P10.16mm_Horizontal
R72: 4k7; Resistor_THT_L6.3mm_D2.5mm_P10.16mm_Horizontal
U2: TL072; DIP-8_W7.62mm_LongPads
U7: LM13700; DIP-16_W7.62mm_LongPads

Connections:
/OutputVCA/I_Gain: U7.16; also elsewhere on the board
/OutputVCA/Input: R68.1; also elsewhere on the board
/OutputVCA/Output: R71.2, R72.2, U2.1; also elsewhere on the board
GND: R69.2, R70.2, U2.3 (+); also elsewhere on the board
unnamed: J27.1, R71.1
unnamed: J27.2, R72.1
unnamed: J27.3, U2.2 (-), U7.12
unnamed: R68.2, R69.1, U7.13 (-)
unnamed: R70.1, U7.14 (+)

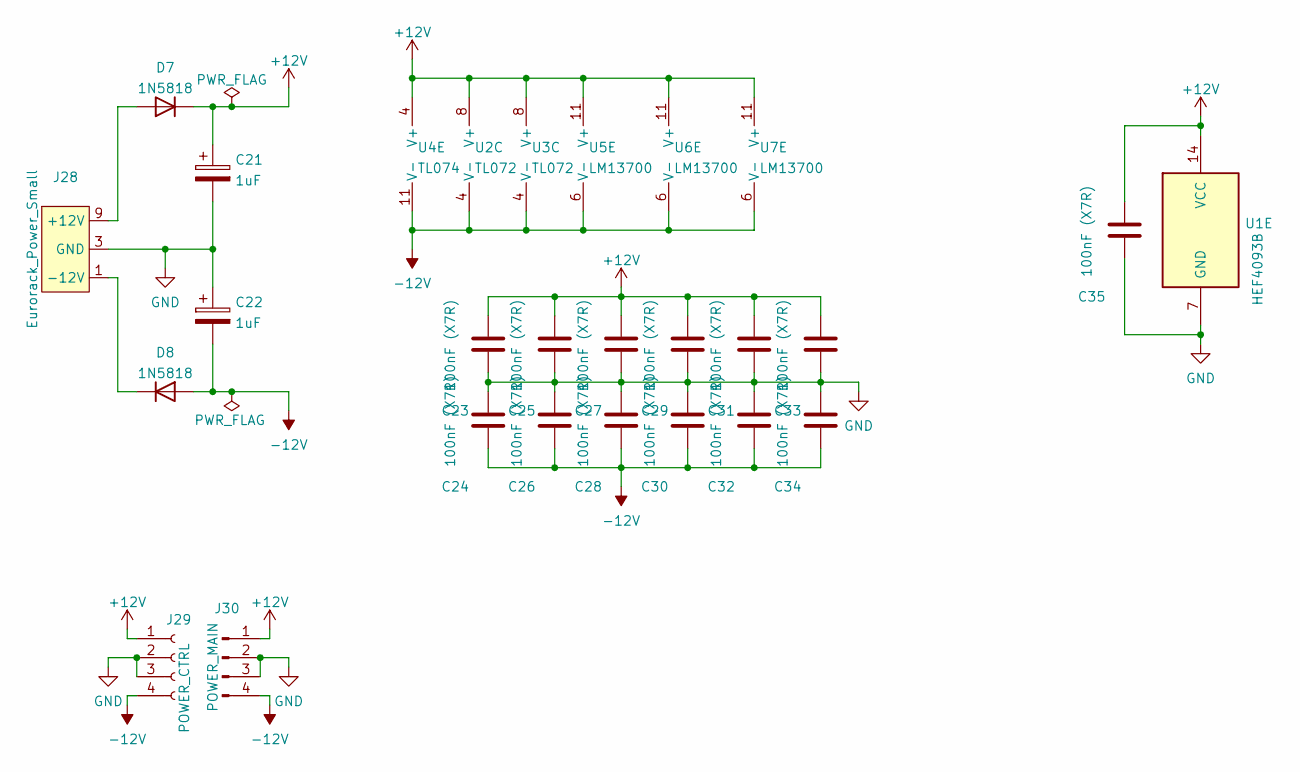
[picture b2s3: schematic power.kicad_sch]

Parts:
C21, C22: 1uF; CP_Radial_D5.0mm_P2.50mm
C23, C24, C25, C26, C27, C28, C29, C30, C31, C32, C33, C34, C35: 100nF (X7R); C_Rect_L7.0mm_W3.5mm_P5.00mm
D7, D8: 1N5818; D_DO-35_SOD27_P7.62mm_Horizontal
J28: Eurorack_Power_Small; Eurorack_PowerHeader_2x05_P2.54mm_Shrouded
J29: POWER_CTRL; PinSocket_1x04_P2.54mm_Vertical
J30: POWER_MAIN; PinHeader_1x04_P2.54mm_Vertical
U1: HEF4093B; DIP-14_W7.62mm_LongPads
U2, U3: TL072; DIP-8_W7.62mm_LongPads
U4: TL074; DIP-14_W7.62mm_LongPads
U5, U6, U7: LM13700; DIP-16_W7.62mm_LongPads

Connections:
+12V: C21.1, C23.1, C25.1, C27.1, C29.1, C31.1, C33.1, C35.1, D7.1 (K), J29.1, J30.1, U1.14 (VCC), U2.8 (V+), U3.8 (V+), U4.4 (V+), U5.11 (V+), U6.11 (V+), U7.11 (V+); also elsewhere on the board
-12V: C22.2, C24.2, C26.2, C28.2, C30.2, C32.2, C34.2, D8.2 (A), J29.4, J30.4, U2.4 (V-), U3.4 (V-), U4.11 (V-), U5.6 (V-), U6.6 (V-), U7.6 (V-); also elsewhere on the board
GND: C21.2, C22.1, C23.2, C24.1, C25.2, C26.1, C27.2, C28.1, C29.2, C30.1, C31.2, C32.1, C33.2, C34.1, C35.2, J28.3 (GND), J28.4 (GND), J28.5 (GND), J28.6 (GND), J28.7 (GND), J28.8 (GND), J29.2, J29.3, J30.2, J30.3, U1.7 (GND); also elsewhere on the board
unnamed: D7.2 (A), J28.9 (+12V), J28.10 (+12V)
unnamed: D8.1 (K), J28.1 (-12V), J28.2 (-12V)

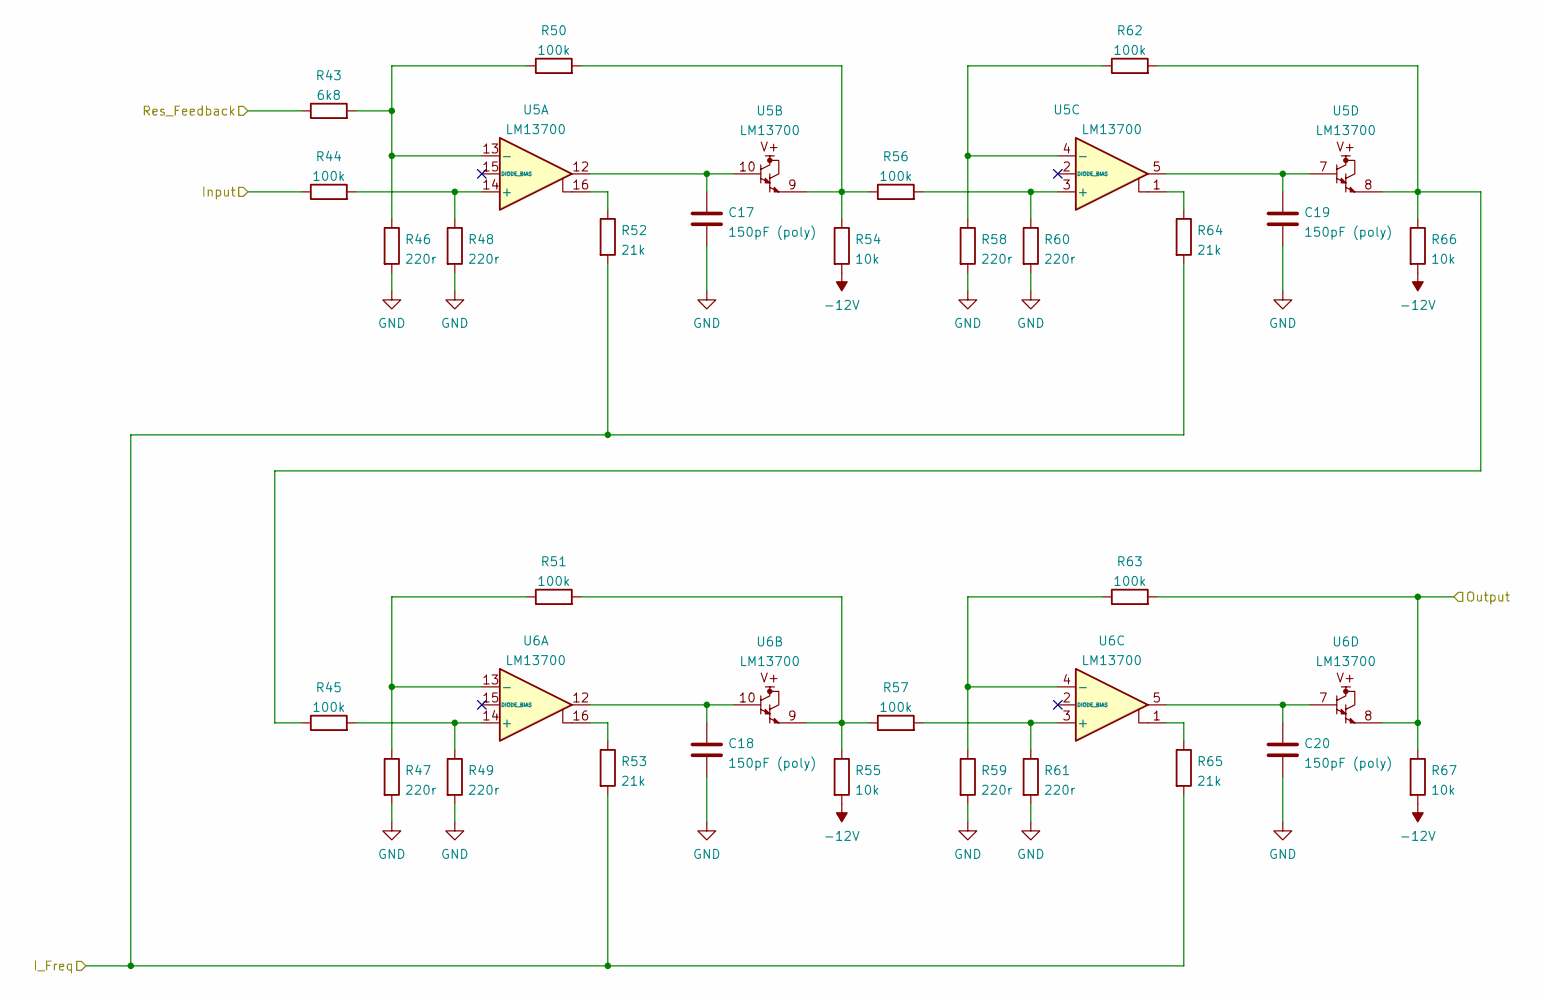
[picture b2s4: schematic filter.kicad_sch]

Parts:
C17, C18, C19, C20: 150pF (poly); C_Rect_L7.0mm_W3.5mm_P5.00mm
R43: 6k8; Resistor_THT_L6.3mm_D2.5mm_P10.16mm_Horizontal
R44, R45, R50, R51, R56, R57, R62, R63: 100k; Resistor_THT_L6.3mm_D2.5mm_P10.16mm_Horizontal
R46, R47, R48, R49, R58, R59, R60, R61: 220r; Resistor_THT_L6.3mm_D2.5mm_P10.16mm_Horizontal
R52, R53, R64, R65: 21k; Resistor_THT_L6.3mm_D2.5mm_P10.16mm_Horizontal
R54, R55, R66, R67: 10k; Resistor_THT_L6.3mm_D2.5mm_P10.16mm_Horizontal
U5, U6: LM13700; DIP-16_W7.62mm_LongPads

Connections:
-12V: R54.2, R55.2, R66.2, R67.2; also elsewhere on the board
/Filter/I_Freq: R52.2, R53.2, R64.2, R65.2; also elsewhere on the board
/Filter/Input: R44.1; also elsewhere on the board
/Filter/Output: R63.2, R67.1, U6.8; also elsewhere on the board
/Res_Amount: R43.1; also elsewhere on the board
GND: C17.1, C18.1, C19.1, C20.1, R46.2, R47.2, R48.2, R49.2, R58.2, R59.2, R60.2, R61.2; also elsewhere on the board
unnamed: C17.2, U5.10, U5.12
unnamed: C18.2, U6.10, U6.12
unnamed: C19.2, U5.5, U5.7
unnamed: C20.2, U6.5, U6.7
unnamed: R43.2, R46.1, R50.1, U5.13 (-)
unnamed: R44.2, R48.1, U5.14 (+)
unnamed: R45.1, R62.2, R66.1, U5.8
unnamed: R45.2, R49.1, U6.14 (+)
unnamed: R47.1, R51.1, U6.13 (-)
unnamed: R50.2, R54.1, R56.1, U5.9
unnamed: R51.2, R55.1, R57.1, U6.9
unnamed: R52.1, U5.16
unnamed: R53.1, U6.16
unnamed: R56.2, R60.1, U5.3 (+)
unnamed: R57.2, R61.1, U6.3 (+)
unnamed: R58.1, R62.1, U5.4 (-)
unnamed: R59.1, R63.1, U6.4 (-)
unnamed: R64.1, U5.1
unnamed: R65.1, U6.1

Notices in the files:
kicad/filter.kicad_sch:
creativecommons.org/licenses/by/4.0
License: CC BY 4.0
